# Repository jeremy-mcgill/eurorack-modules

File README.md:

# Eurorack Modules

## BufferedMult
A 1-in 4-out buffered multiple using a TL084 quad op-amp. 

## Clock
**Note: this is a work in progress, untested and unbuilt**

A master clock/divider module built around an Arduino Nano. 

## Mixer
**Note: this is a work in progress, untested and unbuilt**

A 4-input mixer based on a TL082 dual op-amp, with individual input gain controls and a master output control.

## PassiveMult
Dual passive 1-in 3-out multiples. Bottom section is normalled to top input, so the module can also be used as a single 1-in 6-out multiple. 

## Sequencer
**Note: this is a work in progress, untested and unbuilt**

An 8/16 step sequencer built around an Arduino Nano.

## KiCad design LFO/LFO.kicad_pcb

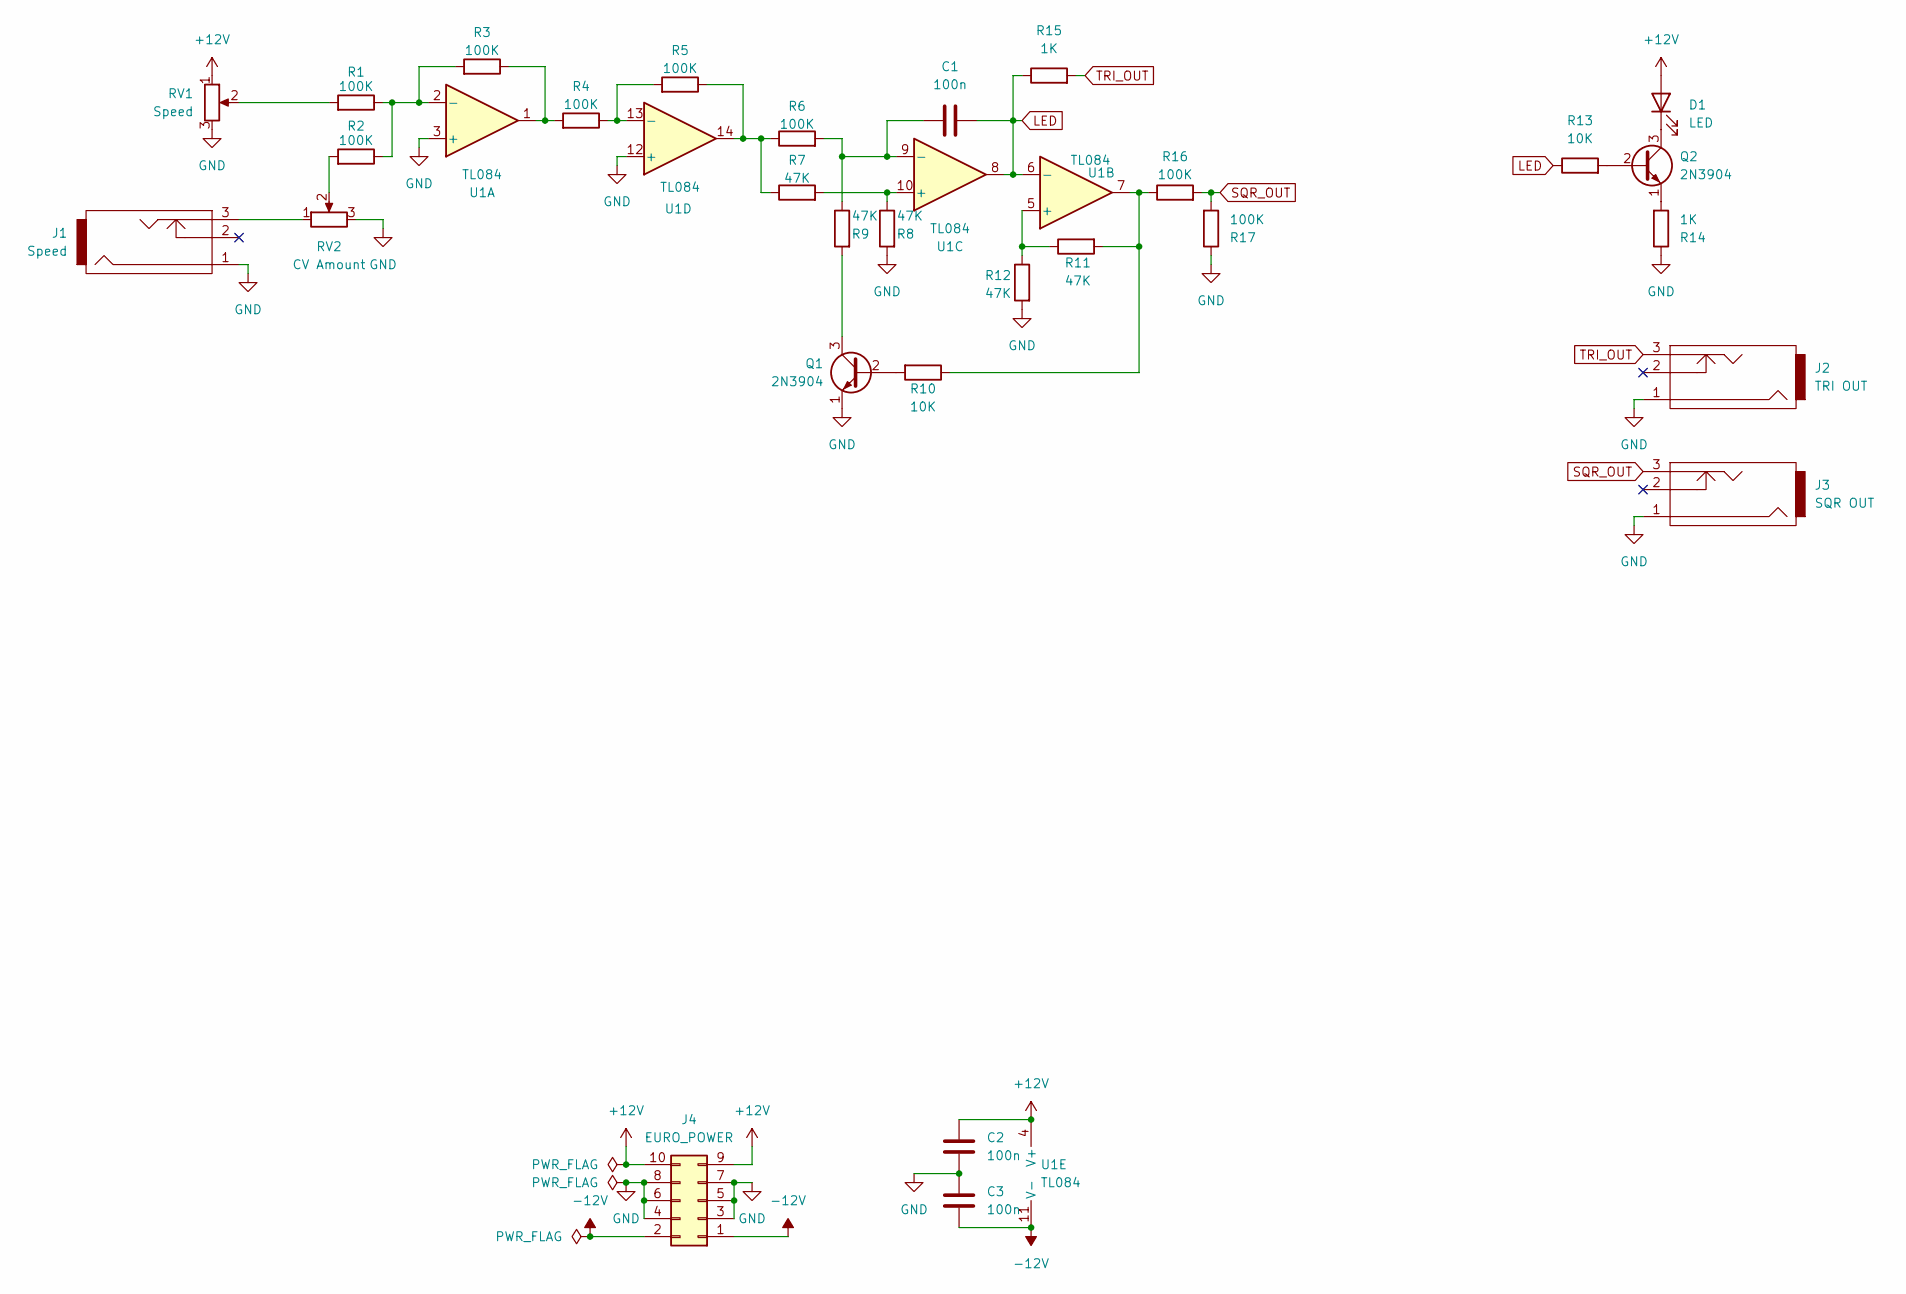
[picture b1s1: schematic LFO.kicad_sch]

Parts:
C1, C2, C3: 100n; C_Disc_D4.7mm_W2.5mm_P5.00mm
D1: LED; LED_D5.0mm
J1: Speed; PJ301M-12
J2: TRI OUT; PJ301M-12
J3: SQR OUT; PJ301M-12
J4: EURO_POWER; PinHeader_2x05_P2.54mm_Vertical
Q1, Q2: 2N3904; TO-92_Inline
R1, R2, R3, R4, R5, R6, R16, R17: 100K; R_Axial_DIN0207_L6.3mm_D2.5mm_P2.54mm_Vertical
R7, R8, R9, R11, R12: 47K; R_Axial_DIN0207_L6.3mm_D2.5mm_P2.54mm_Vertical
R10, R13: 10K; R_Axial_DIN0207_L6.3mm_D2.5mm_P2.54mm_Vertical
R14, R15: 1K; R_Axial_DIN0207_L6.3mm_D2.5mm_P2.54mm_Vertical
RV1: Speed; Potentiometer_Bourns_PTV09A-1_Single_Vertical
RV2: CV Amount; Potentiometer_Bourns_PTV09A-1_Single_Vertical
U1: TL084; DIP-14_W7.62mm_Socket

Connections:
+12V: C2.1, D1.2 (A), J4.9, J4.10, RV1.1, U1.4 (V+)
-12V: C3.2, J4.1, J4.2, U1.11 (V-)
GND: C2.2, C3.1, J1.1, J2.1, J3.1, J4.3, J4.4, J4.5, J4.6, J4.7, J4.8, Q1.1 (E), R8.2, R12.2, R14.1, R17.1, RV1.3, RV2.3, U1.3 (+), U1.12 (+)
LED: C1.2, R13.1, R15.1, U1.6 (-), U1.8
unnamed: D1.1 (K), Q2.3 (C)
unnamed: J1.3, RV2.1
unnamed: Q1.2 (B), R10.2
unnamed: Q1.3 (C), R9.2
unnamed: Q2.2 (B), R13.2
unnamed: Q2.1 (E), R14.2
unnamed: R1.2, RV1.2
unnamed: R2.2, RV2.2
unnamed: R3.1, R4.2, U1.1
unnamed: R5.1, R6.1, R7.1, U1.14
unnamed: R10.1, R11.2, R16.1, U1.7
unnamed: R1.1, R2.1, R3.2, U1.2 (-)
unnamed: R11.1, R12.1, U1.5 (+)
unnamed: R7.2, R8.1, U1.10 (+)
unnamed: C1.1, R6.2, R9.1, U1.9 (-)
unnamed: R4.1, R5.2, U1.13 (-)
SQR_OUT: J3.3, R16.2, R17.2
TRI_OUT: J2.3, R15.2

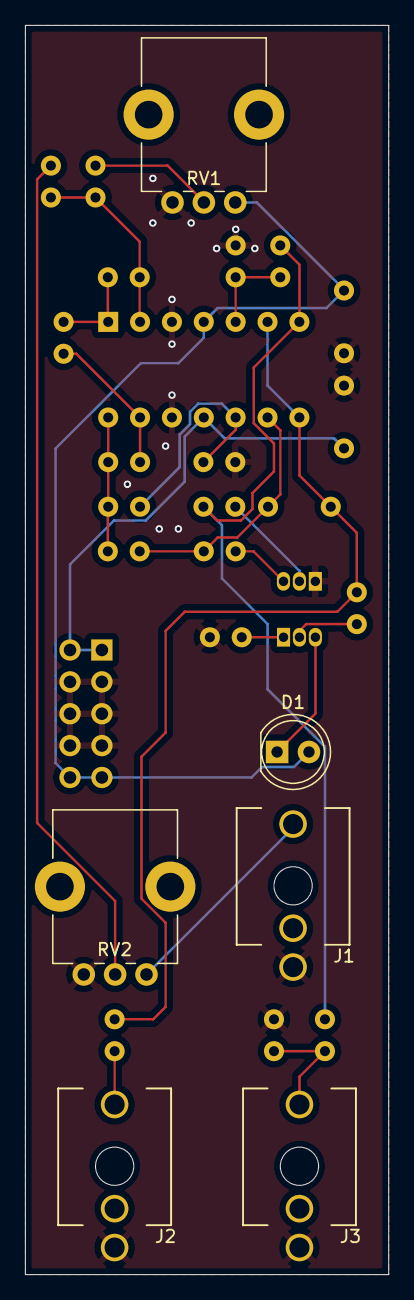
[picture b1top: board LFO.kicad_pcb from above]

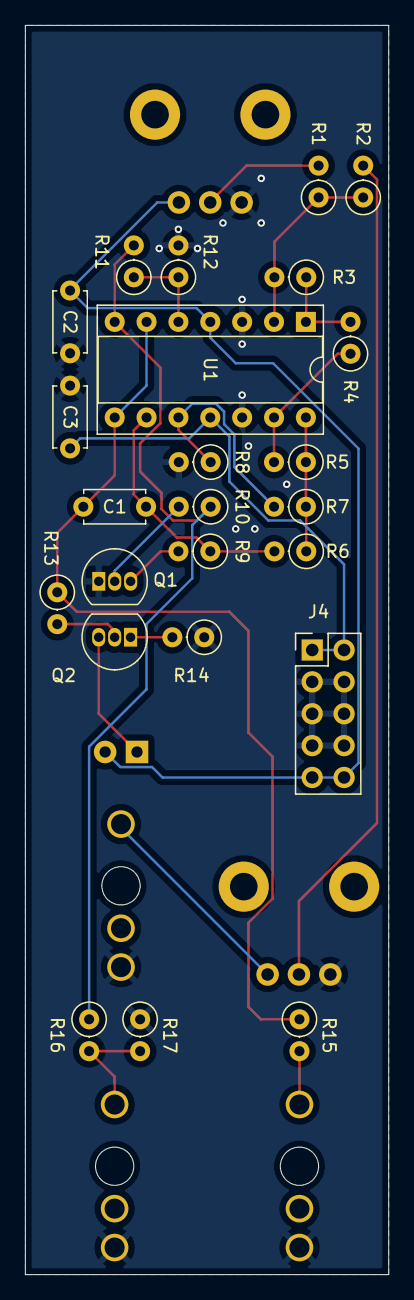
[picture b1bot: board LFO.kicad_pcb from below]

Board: 2 copper layers, 29.0 x 99.6 mm, 30 parts (24 on the bottom side), 22 nets.

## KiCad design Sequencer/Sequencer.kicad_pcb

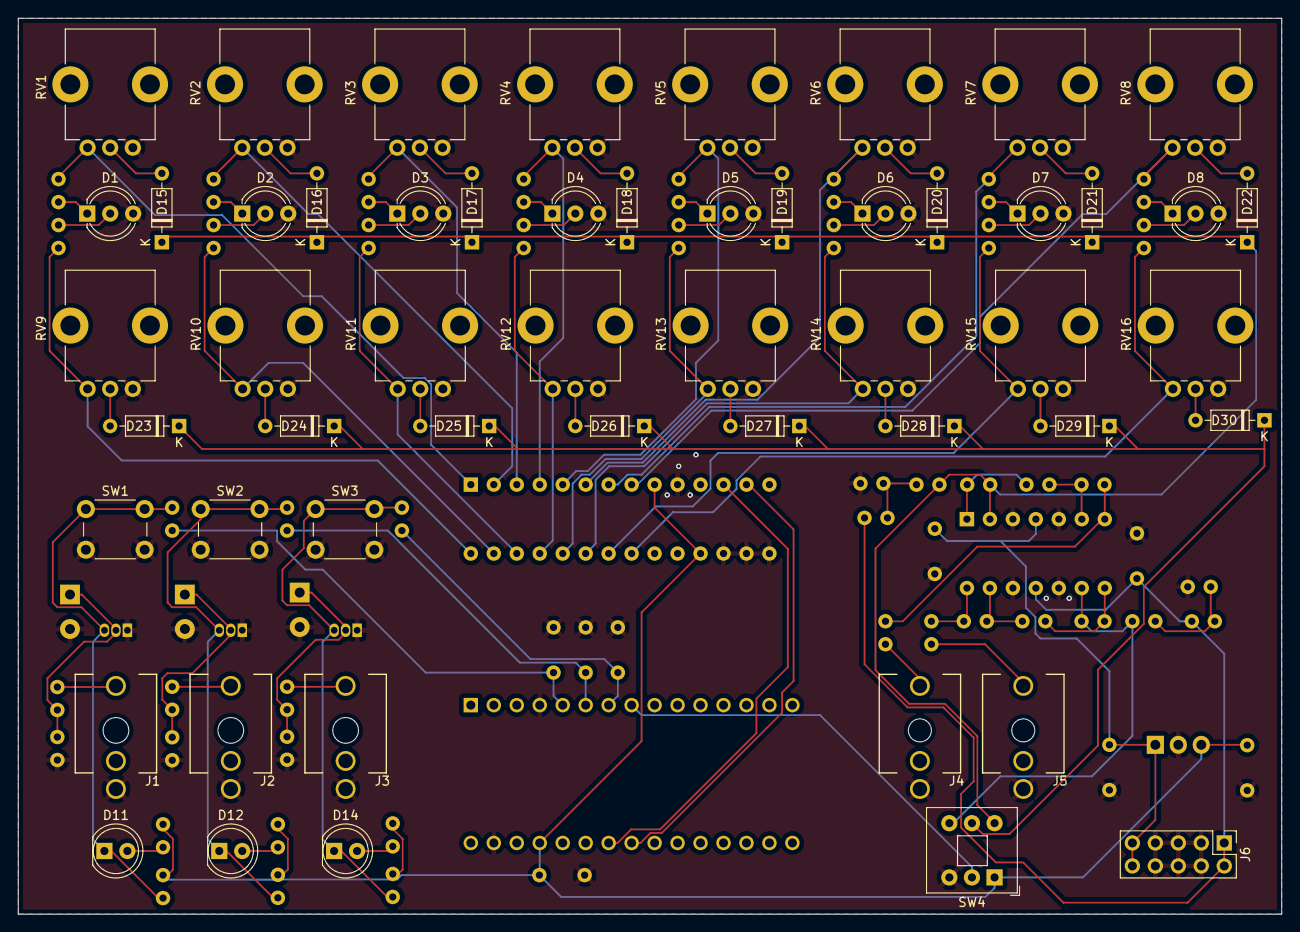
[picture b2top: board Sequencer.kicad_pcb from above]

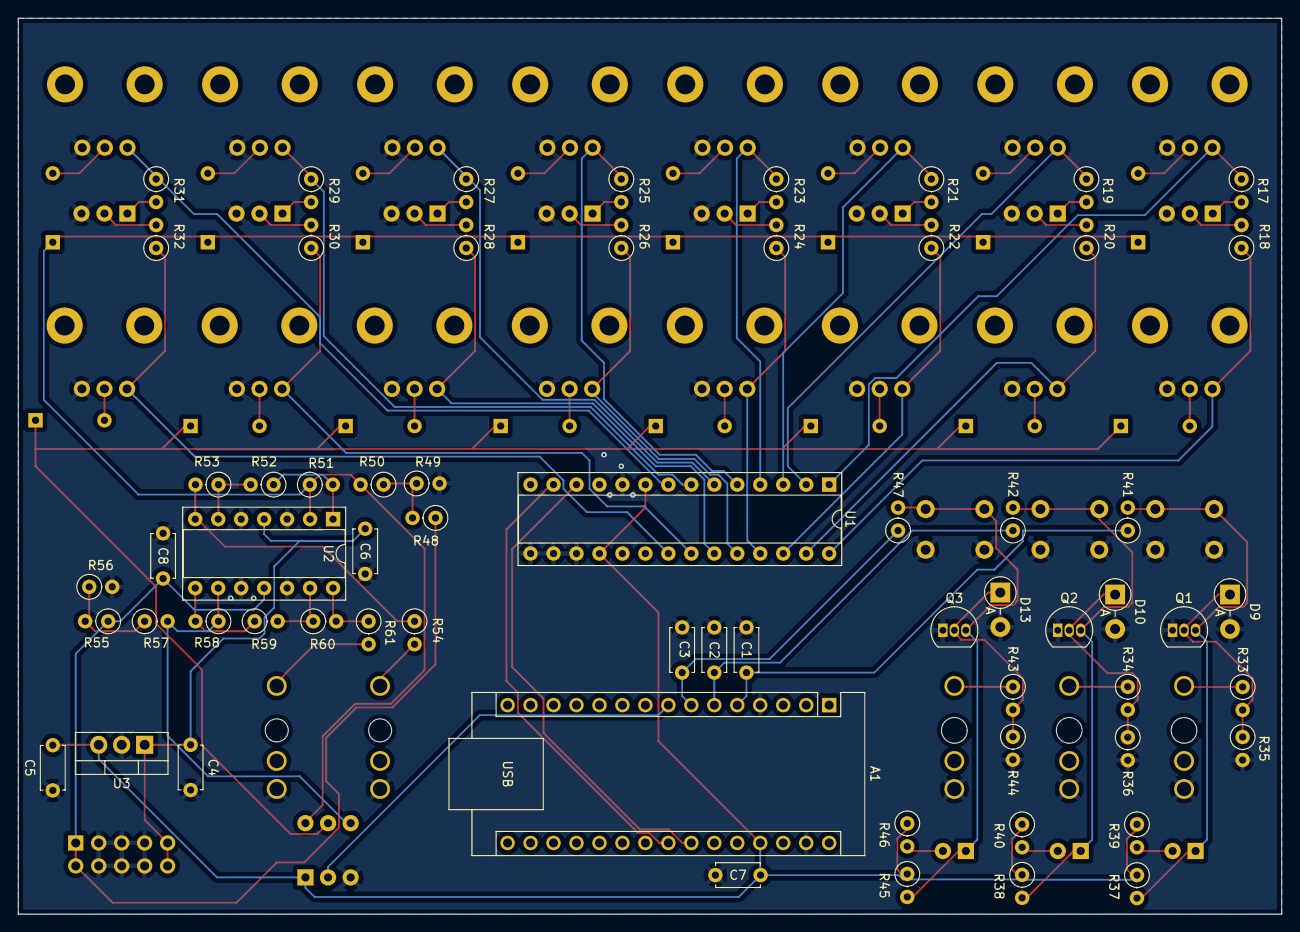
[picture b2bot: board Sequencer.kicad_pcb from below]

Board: 2 copper layers, 139.7 x 99.1 mm, 116 parts (63 on the bottom side), 83 nets.

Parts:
A1: Arduino_Nano_v3.x; Arduino_Nano
C1, C2, C3: 220nF; C_Disc_D4.7mm_W2.5mm_P5.00mm
C4: .33uF; C_Disc_D4.7mm_W2.5mm_P5.00mm
C5: .1uF; C_Disc_D4.7mm_W2.5mm_P5.00mm
C6, C7, C8: 100n; C_Disc_D4.7mm_W2.5mm_P5.00mm
D1, D2, D3, D4, D5, D6, D7, D8: LED_Dual_AAK; LED_D5.0mm-3
D9, D10, D13: 1N5817; D_DO-41_SOD81_P3.81mm_Vertical_AnodeUp
D11: LED_STEP; LED_D5.0mm_Clear
D12: LED_RESET; LED_D5.0mm_Clear
D14: LED_FLIP; LED_D5.0mm_Clear
D15, D16, D17, D18, D19, D20, D21, D22, D23, D24, D25, D26, D27, D28, D29, D30: 1N4148; D_DO-35_SOD27_P7.62mm_Horizontal
J1: CLOCK_IN; PJ301M-12
J2: RESET_IN; PJ301M-12
J3: FLIP_IN; PJ301M-12
J4: CV1_OUT; PJ301M-12
J5: CV2_OUT; PJ301M-12
J6: Power; PinHeader_2x05_P2.54mm_Vertical
Q1, Q2, Q3: 2N3904; TO-92_Inline
R17, R18, R19, R20, R21, R22, R23, R24, R25, R26, R27, R28, R29, R30, R31, R32, R39, R40, R46: 560R; R_Axial_DIN0207_L6.3mm_D2.5mm_P2.54mm_Vertical
R33, R34, R43, R50, R57: 100K; R_Axial_DIN0207_L6.3mm_D2.5mm_P2.54mm_Vertical
R35, R36, R44: 1M; R_Axial_DIN0207_L6.3mm_D2.5mm_P2.54mm_Vertical
R37, R38, R45, R52, R53, R59, R60: 10K; R_Axial_DIN0207_L6.3mm_D2.5mm_P2.54mm_Vertical
R41, R42, R47, R54, R61: 1K; R_Axial_DIN0207_L6.3mm_D2.5mm_P2.54mm_Vertical
R48, R55: 68K; R_Axial_DIN0207_L6.3mm_D2.5mm_P2.54mm_Vertical
R49, R56: 18K; R_Axial_DIN0207_L6.3mm_D2.5mm_P2.54mm_Vertical
R51, R58: 220K; R_Axial_DIN0207_L6.3mm_D2.5mm_P2.54mm_Vertical
RV1, RV2, RV3, RV4, RV5, RV6, RV7, RV8, RV9, RV10, RV11, RV12, RV13, RV14, RV15, RV16: A10K; Potentiometer_Bourns_PTV09A-1_Single_Vertical
SW1: SW_STEP; SW_PUSH_6mm
SW2: SW_RESET; SW_PUSH_6mm
SW3: SW_FLIP; SW_PUSH_6mm
SW4: SW_8/16; SW_Push_2P2T_Toggle_CK_PVA2xxH2xxxxxxV2
U1: MCP23017_SP; DIP-28_W7.62mm_Socket
U2: TL084; DIP-14_W7.62mm_Socket
U3: L7805; TO-220-3_Vertical

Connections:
+5V: A1.27 (+5V), C5.1, C7.1, R37.1, R38.1, R39.1, R40.1, R45.1, R46.1, SW4.1 (A), U1.9 (VDD), U1.18 (~RESET), U3.3 (OUT)
+12V: C4.1, C6.1, J6.9, J6.10, U2.4 (V+), U3.1 (IN)
-12V: C8.2, J6.1, J6.2, R48.1, R55.1, U2.11 (V-)
CLOCK_IN: A1.5 (D2), C1.1, R41.1
CV1_OUT: D15.1 (K), D16.1 (K), D17.1 (K), D18.1 (K), D19.1 (K), D20.1 (K), D21.1 (K), D22.1 (K), R50.2, R51.1, SW4.4 (A), U2.2 (-)
CV2_OUT: R57.2, R58.1, SW4.6 (C), U2.9 (-)
FLIP_IN: A1.7 (D4), C3.1, R47.1
GND: A1.4 (GND), A1.29 (GND), C1.2, C2.2, C3.2, C4.2, C5.2, C6.2, C7.2, C8.1, D1.3 (K), D2.3 (K), D3.3 (K), D4.3 (K), D5.3 (K), D6.3 (K), D7.3 (K), D8.3 (K), D9.2 (A), D10.2 (A), D13.2 (A), J1.1, J2.1, J3.1, J4.1, J5.1, J6.3, J6.4, J6.5, J6.6, J6.7, J6.8, Q1.1 (E), Q2.1 (E), Q3.1 (E), R35.2, R36.2, R44.2, R49.2, R56.2, RV1.1, RV2.1, RV3.1, RV4.1, RV5.1, RV6.1, RV7.1, RV8.1, RV9.1, RV10.1, RV11.1, RV12.1, RV13.1, RV14.1, RV15.1, RV16.1, SW1.2, SW2.2, SW3.2, SW4.3 (C), U1.10 (VSS), U1.15 (A0), U1.16 (A1), U1.17 (A2), U2.3 (+), U2.5 (+), U2.10 (+), U2.12 (+), U3.2 (GND)
unnamed: D1.1 (A1), R17.2
unnamed: D1.2 (A2), R18.2
unnamed: D2.1 (A1), R19.2
unnamed: D2.2 (A2), R20.2
unnamed: D3.1 (A1), R21.2
unnamed: D3.2 (A2), R22.2
unnamed: D4.1 (A1), R23.2
unnamed: D4.2 (A2), R24.2
unnamed: D5.1 (A1), R25.2
unnamed: D5.2 (A2), R26.2
unnamed: D6.1 (A1), R27.2
unnamed: D6.2 (A2), R28.2
unnamed: D7.1 (A1), R29.2
unnamed: D7.2 (A2), R30.2
unnamed: D8.1 (A1), R31.2
unnamed: D8.2 (A2), R32.2
unnamed: D9.1 (K), Q1.2 (B), R33.2, R35.1
unnamed: D10.1 (K), Q2.2 (B), R34.2, R36.1
unnamed: D11.2 (A), R39.2
unnamed: D11.1 (K), Q1.3 (C), R37.2, R41.2, SW1.1
unnamed: D12.2 (A), R40.2
unnamed: D12.1 (K), Q2.3 (C), R38.2, R42.2, SW2.1
unnamed: D13.1 (K), Q3.2 (B), R43.2, R44.1
unnamed: D14.2 (A), R46.2
unnamed: D14.1 (K), Q3.3 (C), R45.2, R47.2, SW3.1
unnamed: D15.2 (A), RV1.2
unnamed: D16.2 (A), RV2.2
unnamed: D17.2 (A), RV3.2
unnamed: D18.2 (A), RV4.2
unnamed: D19.2 (A), RV5.2
unnamed: D20.2 (A), RV6.2
unnamed: D21.2 (A), RV7.2
unnamed: D22.2 (A), RV8.2
unnamed: D23.2 (A), RV9.2
unnamed: D23.1 (K), D24.1 (K), D25.1 (K), D26.1 (K), D27.1 (K), D28.1 (K), D29.1 (K), D30.1 (K), SW4.5 (B)
unnamed: D24.2 (A), RV10.2
unnamed: D25.2 (A), RV11.2
unnamed: D26.2 (A), RV12.2
unnamed: D27.2 (A), RV13.2
unnamed: D28.2 (A), RV14.2
unnamed: D29.2 (A), RV15.2
unnamed: D30.2 (A), RV16.2
unnamed: J1.3, R33.1
unnamed: J2.3, R34.1
unnamed: J3.3, R43.1
unnamed: J4.3, R54.2
unnamed: J5.3, R61.2
unnamed: R48.2, R49.1, R50.1
unnamed: R51.2, R52.1, U2.1
unnamed: R53.2, R54.1, U2.7
unnamed: R55.2, R56.1, R57.1
unnamed: R58.2, R59.1, U2.8
unnamed: R60.2, R61.1, U2.14
unnamed: R52.2, R53.1, U2.6 (-)
unnamed: R59.2, R60.1, U2.13 (-)
RESET_IN: A1.6 (D3), C2.1, R42.1
SCK: A1.24 (A5), U1.12 (SCK)
SDA: A1.23 (A4), U1.13 (SDA)
STEP1: R17.1, RV1.3, U1.1 (GPB0)
STEP2: R19.1, RV2.3, U1.2 (GPB1)
STEP3: R21.1, RV3.3, U1.3 (GPB2)
STEP4: R23.1, RV4.3, U1.4 (GPB3)
STEP5: R25.1, RV5.3, U1.5 (GPB4)
STEP6: R27.1, RV6.3, U1.6 (GPB5)
STEP7: R29.1, RV7.3, U1.7 (GPB6)
STEP8: R31.1, RV8.3, U1.8 (GPB7)
STEP9: R18.1, RV9.3, U1.28 (GPA7)
STEP10: R20.1, RV10.3, U1.27 (GPA6)
STEP11: R22.1, RV11.3, U1.26 (GPA5)
STEP12: R24.1, RV12.3, U1.25 (GPA4)
STEP13: R26.1, RV13.3, U1.24 (GPA3)
STEP14: R28.1, RV14.3, U1.23 (GPA2)
STEP15: R30.1, RV15.3, U1.22 (GPA1)
STEP16: R32.1, RV16.3, U1.21 (GPA0)
STEP_MODE: A1.8 (D5), SW4.2 (B)

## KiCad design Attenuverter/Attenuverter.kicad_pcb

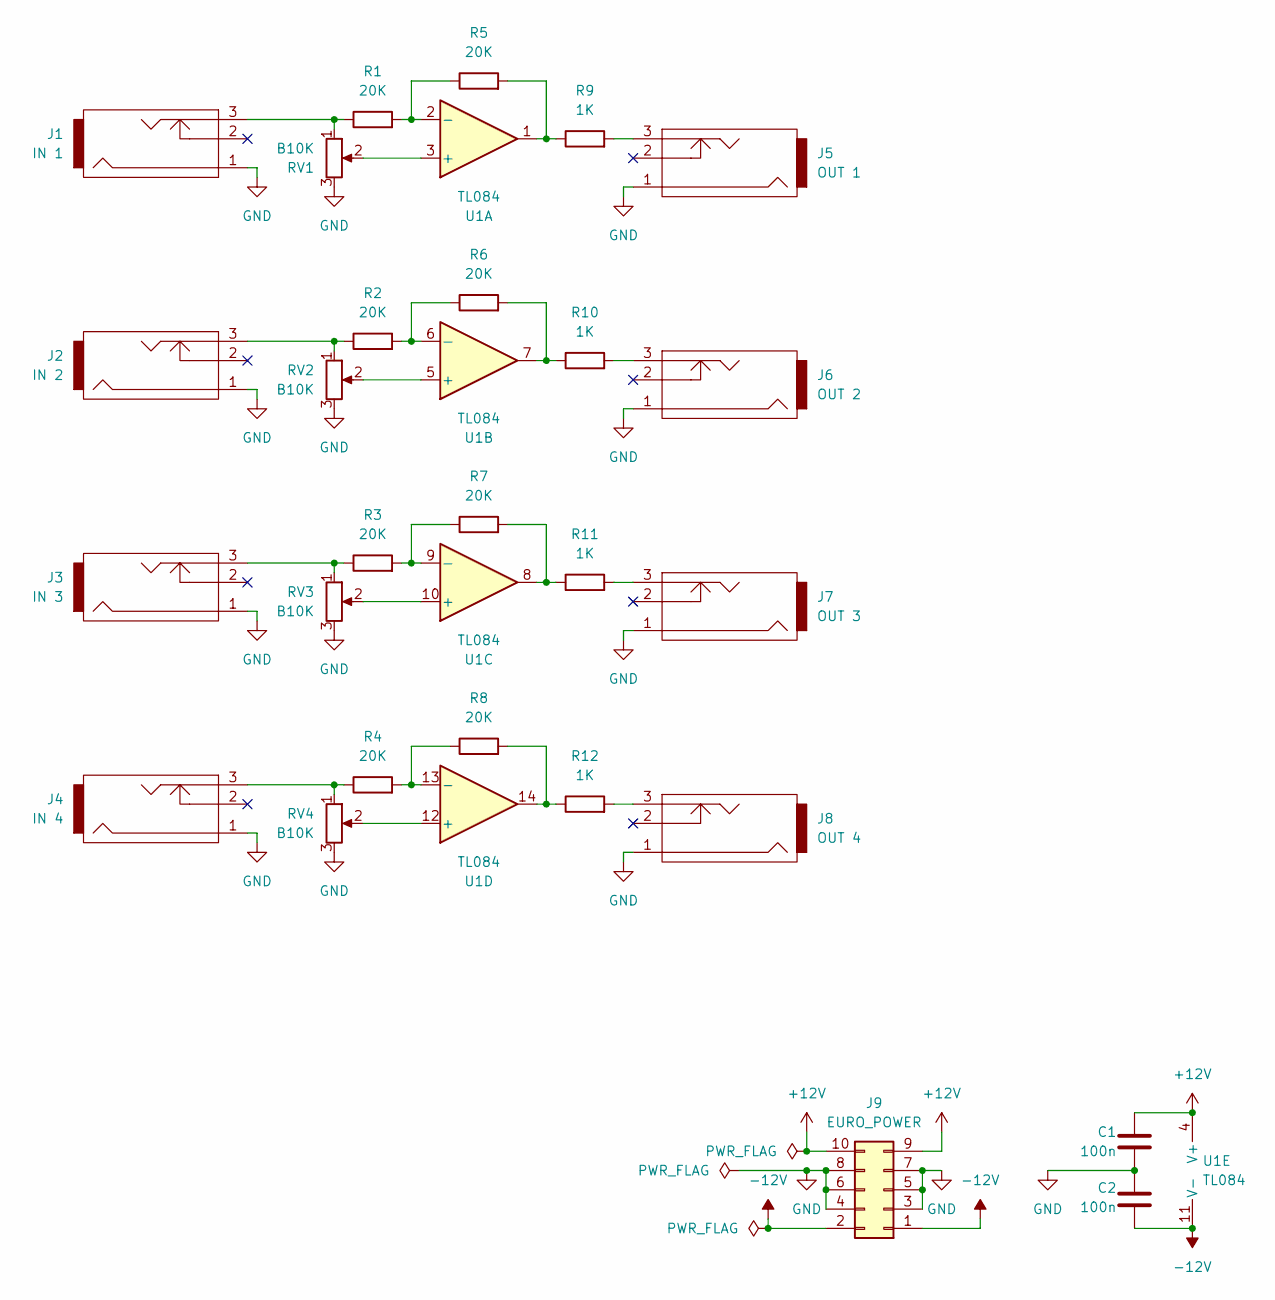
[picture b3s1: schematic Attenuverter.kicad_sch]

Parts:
C1, C2: 100n; C_Disc_D3.0mm_W1.6mm_P2.50mm
J1: IN 1; PJ301M-12
J2: IN 2; PJ301M-12
J3: IN 3; PJ301M-12
J4: IN 4; PJ301M-12
J5: OUT 1; PJ301M-12
J6: OUT 2; PJ301M-12
J7: OUT 3; PJ301M-12
J8: OUT 4; PJ301M-12
J9: EURO_POWER; PinHeader_2x05_P2.54mm_Vertical
R1, R2, R3, R4, R5, R6, R7, R8: 20K; R_Axial_DIN0204_L3.6mm_D1.6mm_P2.54mm_Vertical
R9, R10, R11, R12: 1K; R_Axial_DIN0204_L3.6mm_D1.6mm_P2.54mm_Vertical
RV1, RV2, RV3, RV4: B10K; Potentiometer_Bourns_PTV09A-1_Single_Vertical
U1: TL084; DIP-14_W7.62mm_Socket

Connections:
+12V: C1.1, J9.9, J9.10, U1.4 (V+)
-12V: C2.2, J9.1, J9.2, U1.11 (V-)
GND: C1.2, C2.1, J1.1, J2.1, J3.1, J4.1, J5.1, J6.1, J7.1, J8.1, J9.3, J9.4, J9.5, J9.6, J9.7, J9.8, RV1.3, RV2.3, RV3.3, RV4.3
unnamed: J1.3, R1.1, RV1.1
unnamed: J2.3, R2.1, RV2.1
unnamed: J3.3, R3.1, RV3.1
unnamed: J4.3, R4.1, RV4.1
unnamed: J5.3, R9.2
unnamed: J6.3, R10.2
unnamed: J7.3, R11.2
unnamed: J8.3, R12.2
unnamed: R5.2, R9.1, U1.1
unnamed: R6.2, R10.1, U1.7
unnamed: R7.2, R11.1, U1.8
unnamed: R8.2, R12.1, U1.14
unnamed: RV1.2, U1.3 (+)
unnamed: R1.2, R5.1, U1.2 (-)
unnamed: RV2.2, U1.5 (+)
unnamed: R2.2, R6.1, U1.6 (-)
unnamed: RV3.2, U1.10 (+)
unnamed: R3.2, R7.1, U1.9 (-)
unnamed: RV4.2, U1.12 (+)
unnamed: R4.2, R8.1, U1.13 (-)

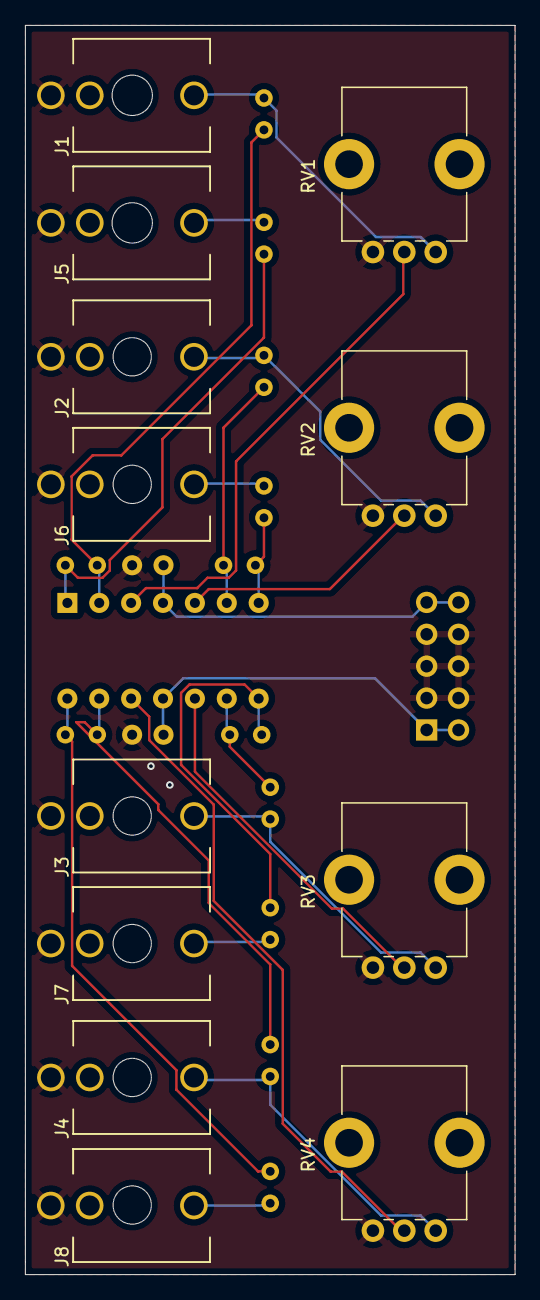
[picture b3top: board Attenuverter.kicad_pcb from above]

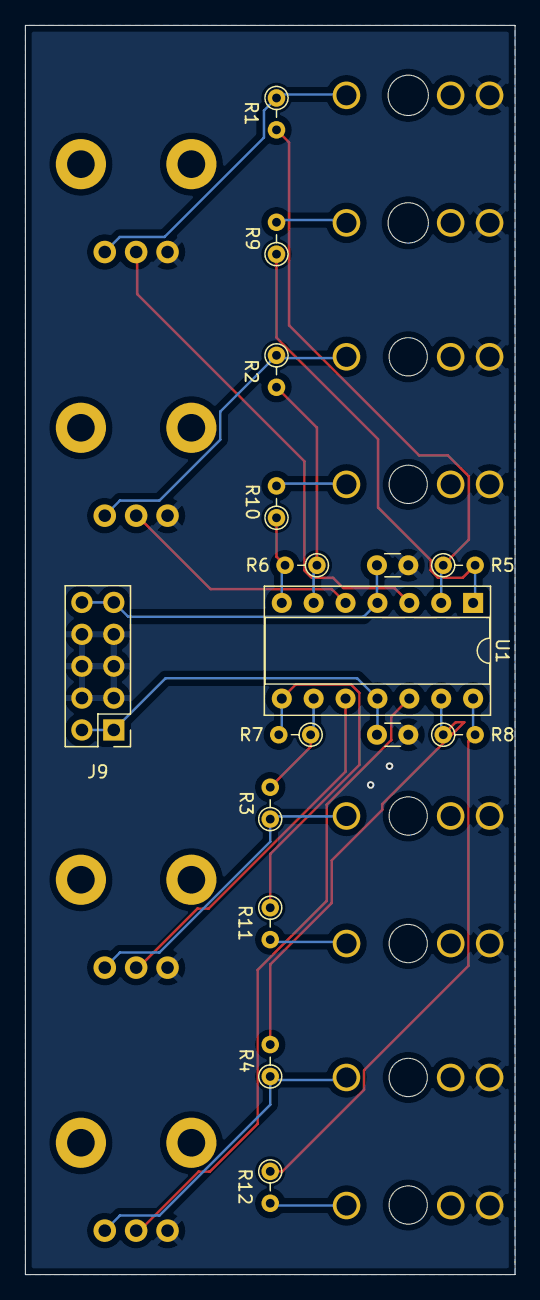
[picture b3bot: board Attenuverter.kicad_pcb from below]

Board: 2 copper layers, 39.0 x 99.5 mm, 28 parts (16 on the bottom side), 23 nets.

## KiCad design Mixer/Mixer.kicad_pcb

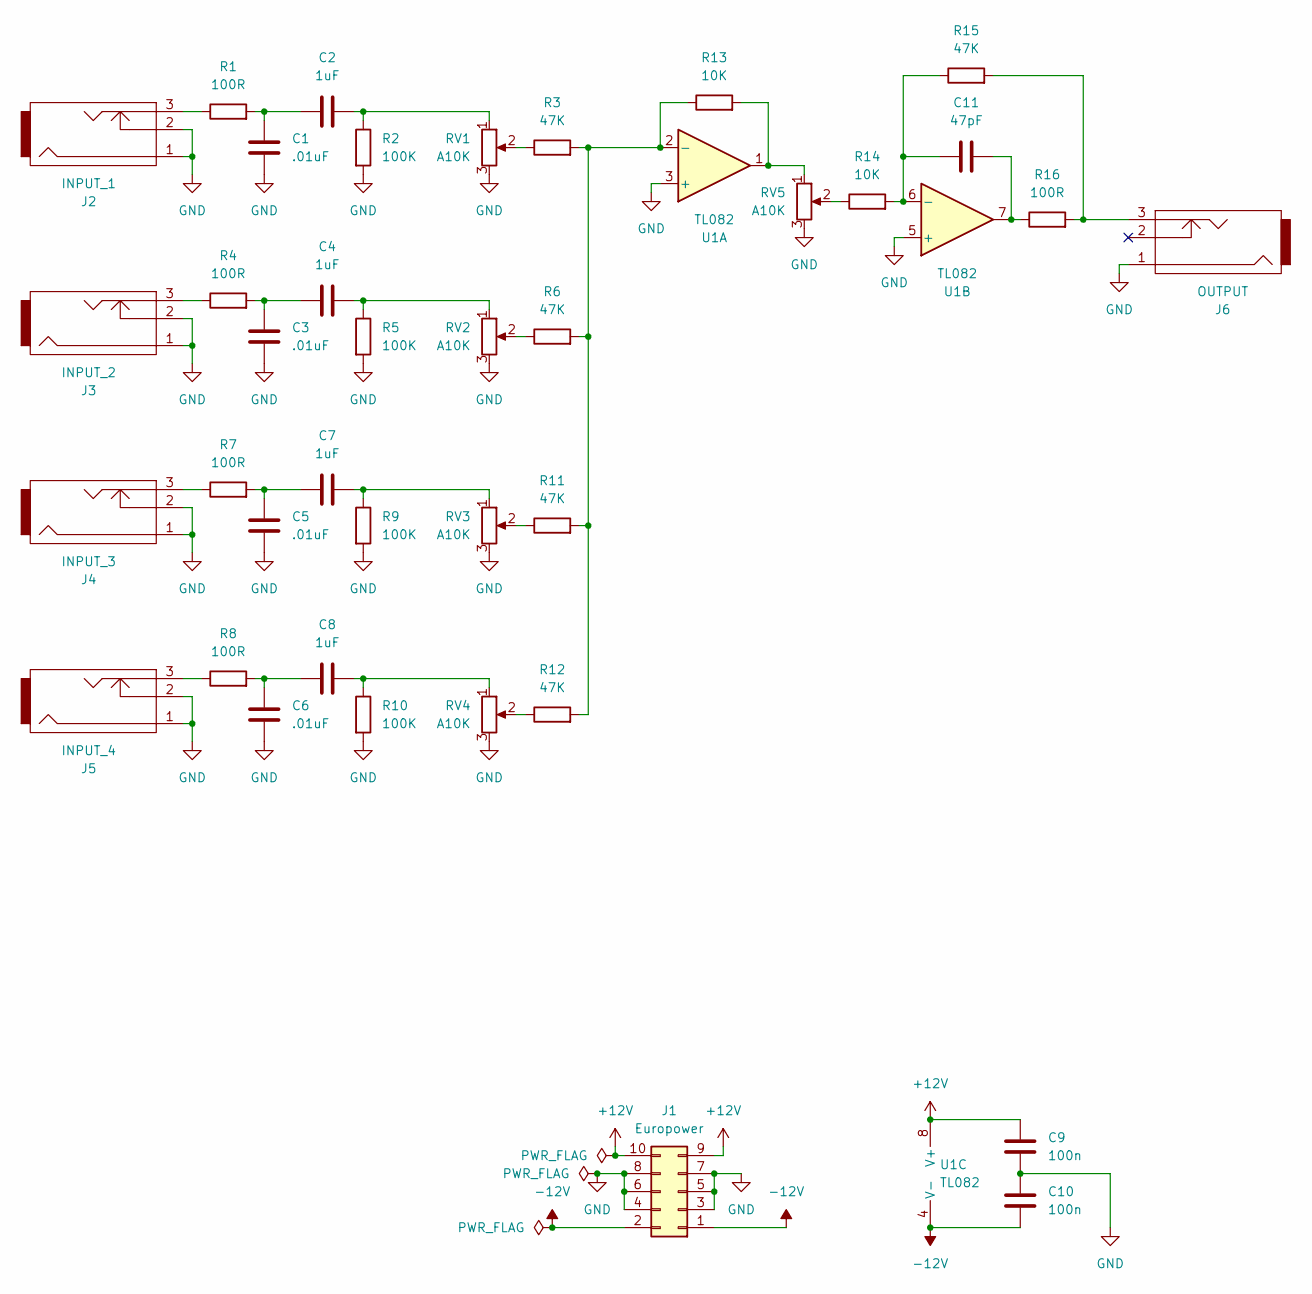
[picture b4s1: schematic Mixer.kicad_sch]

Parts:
C1, C3, C5, C6: .01uF; C_Disc_D4.7mm_W2.5mm_P5.00mm
C2, C4, C7, C8: 1uF; C_Disc_D4.7mm_W2.5mm_P5.00mm
C9, C10: 100n; C_Disc_D4.7mm_W2.5mm_P5.00mm
C11: 47pF; C_Disc_D4.7mm_W2.5mm_P5.00mm
J1: Europower; PinHeader_2x05_P2.54mm_Vertical
J2: INPUT_1; PJ301M-12
J3: INPUT_2; PJ301M-12
J4: INPUT_3; PJ301M-12
J5: INPUT_4; PJ301M-12
J6: OUTPUT; PJ301M-12
R1, R4, R7, R8, R16: 100R; R_Axial_DIN0207_L6.3mm_D2.5mm_P2.54mm_Vertical
R2, R5, R9, R10: 100K; R_Axial_DIN0207_L6.3mm_D2.5mm_P2.54mm_Vertical
R3, R6, R11, R12, R15: 47K; R_Axial_DIN0207_L6.3mm_D2.5mm_P2.54mm_Vertical
R13, R14: 10K; R_Axial_DIN0207_L6.3mm_D2.5mm_P2.54mm_Vertical
RV1, RV2, RV3, RV4, RV5: A10K; Potentiometer_Bourns_PTV09A-1_Single_Vertical
U1: TL082; DIP-8_W7.62mm_Socket

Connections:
+12V: C9.1, J1.9, J1.10, U1.8 (V+)
-12V: C10.2, J1.1, J1.2, U1.4 (V-)
GND: C1.2, C3.2, C5.2, C6.2, C9.2, C10.1, J1.3, J1.4, J1.5, J1.6, J1.7, J1.8, J2.1, J2.2, J3.1, J3.2, J4.1, J4.2, J5.1, J5.2, J6.1, R2.2, R5.2, R9.2, R10.2, RV1.3, RV2.3, RV3.3, RV4.3, RV5.3, U1.3 (+), U1.5 (+)
unnamed: C1.1, C2.1, R1.2
unnamed: C2.2, R2.1, RV1.1
unnamed: C3.1, C4.1, R4.2
unnamed: C4.2, R5.1, RV2.1
unnamed: C5.1, C7.1, R7.2
unnamed: C6.1, C8.1, R8.2
unnamed: C7.2, R9.1, RV3.1
unnamed: C8.2, R10.1, RV4.1
unnamed: C11.2, R16.1, U1.7
unnamed: J2.3, R1.1
unnamed: J3.3, R4.1
unnamed: J4.3, R7.1
unnamed: J5.3, R8.1
unnamed: J6.3, R15.2, R16.2
unnamed: R3.1, RV1.2
unnamed: R6.1, RV2.2
unnamed: R11.1, RV3.2
unnamed: R12.1, RV4.2
unnamed: R13.2, RV5.1, U1.1
unnamed: R14.1, RV5.2
unnamed: R3.2, R6.2, R11.2, R12.2, R13.1, U1.2 (-)
unnamed: C11.1, R14.2, R15.1, U1.6 (-)

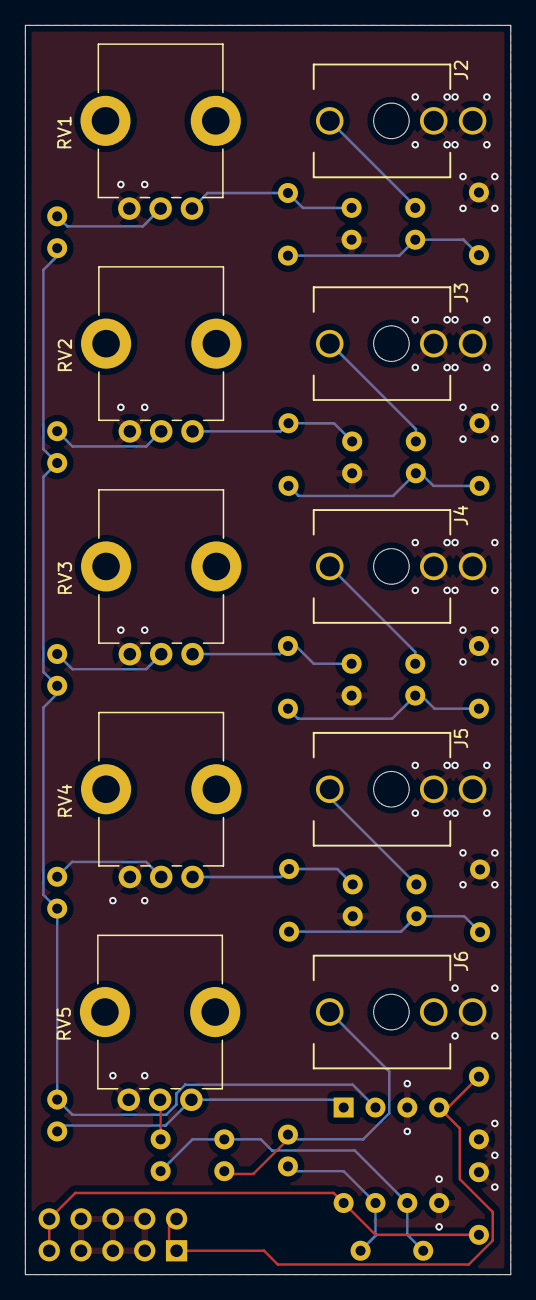
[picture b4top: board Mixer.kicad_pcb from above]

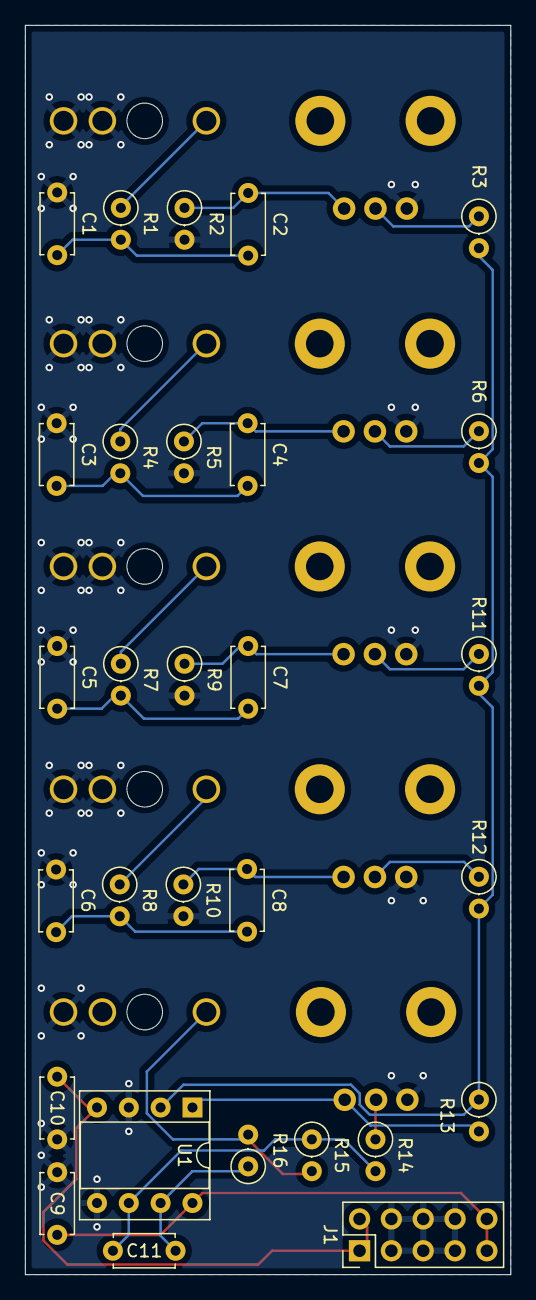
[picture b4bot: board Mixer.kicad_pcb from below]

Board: 2 copper layers, 38.7 x 99.7 mm, 39 parts (29 on the bottom side), 25 nets.

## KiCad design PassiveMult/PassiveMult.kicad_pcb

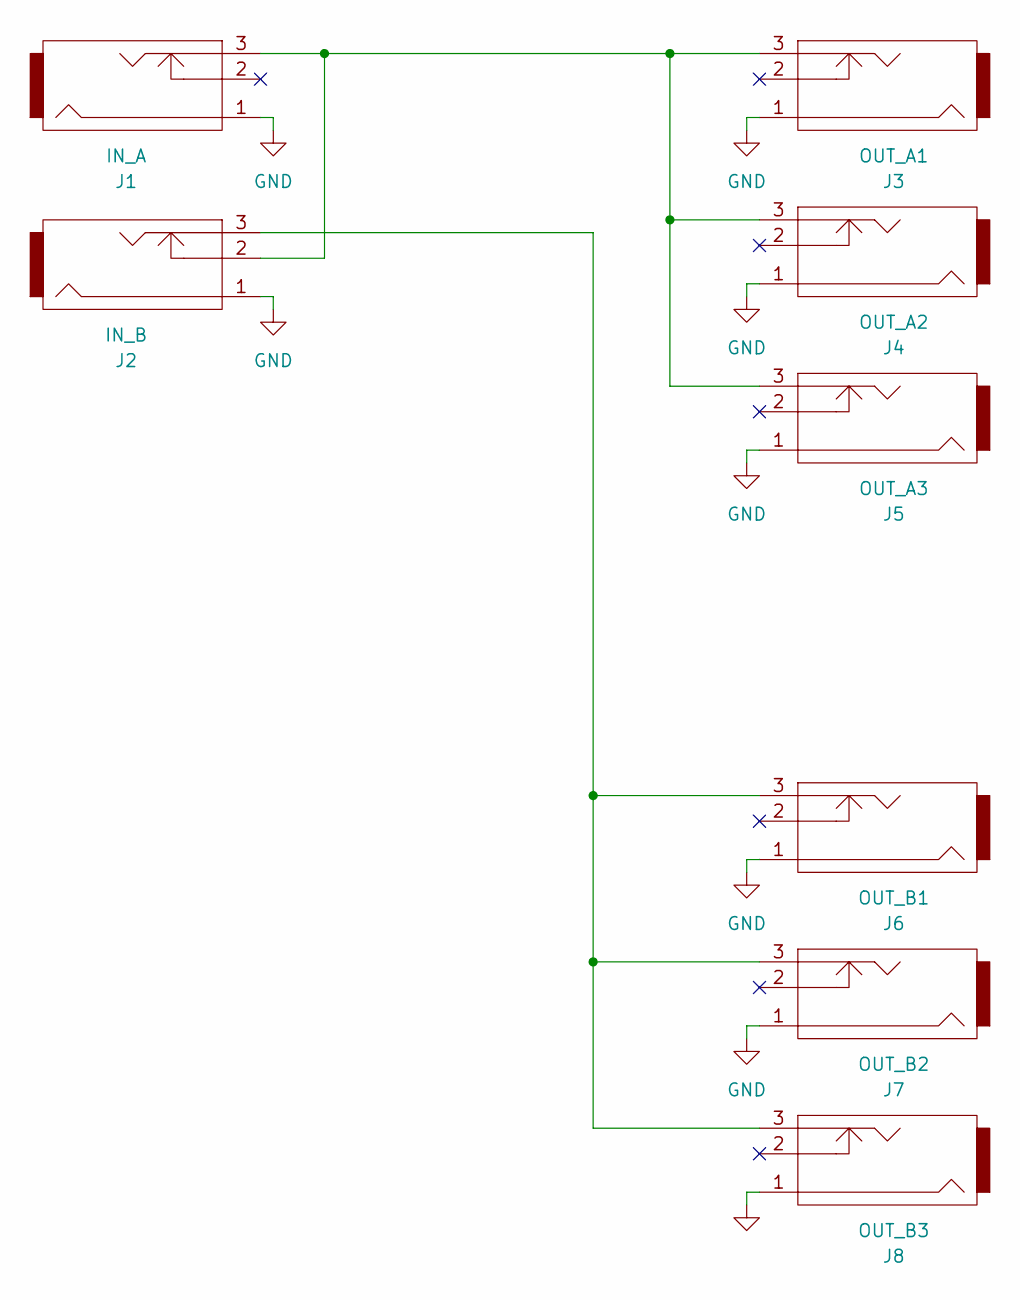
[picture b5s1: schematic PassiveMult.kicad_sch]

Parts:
J1: IN_A; PJ301M-12
J2: IN_B; PJ301M-12
J3: OUT_A1; PJ301M-12
J4: OUT_A2; PJ301M-12
J5: OUT_A3; PJ301M-12
J6: OUT_B1; PJ301M-12
J7: OUT_B2; PJ301M-12
J8: OUT_B3; PJ301M-12

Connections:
GND: J1.1, J2.1, J3.1, J4.1, J5.1, J6.1, J7.1, J8.1
unnamed: J1.3, J2.2, J3.3, J4.3, J5.3
unnamed: J2.3, J6.3, J7.3, J8.3

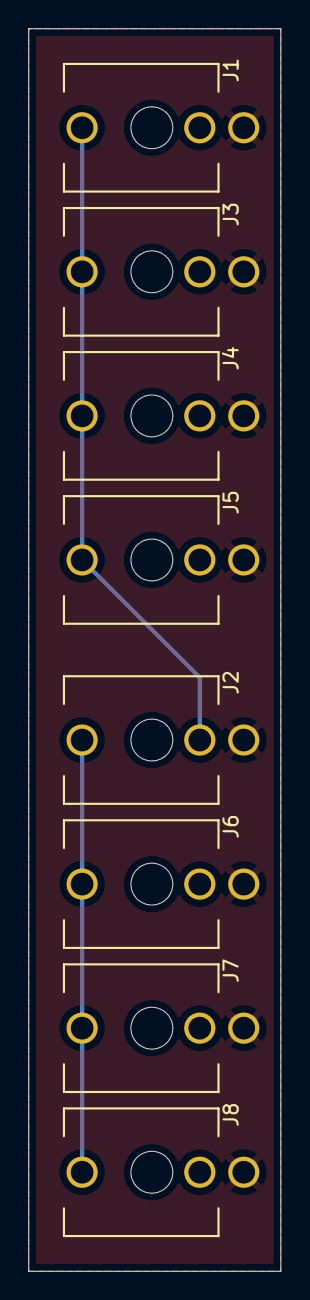
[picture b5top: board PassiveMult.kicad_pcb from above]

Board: 2 copper layers, 17.8 x 87.6 mm, 8 parts (0 on the bottom side), 3 nets.

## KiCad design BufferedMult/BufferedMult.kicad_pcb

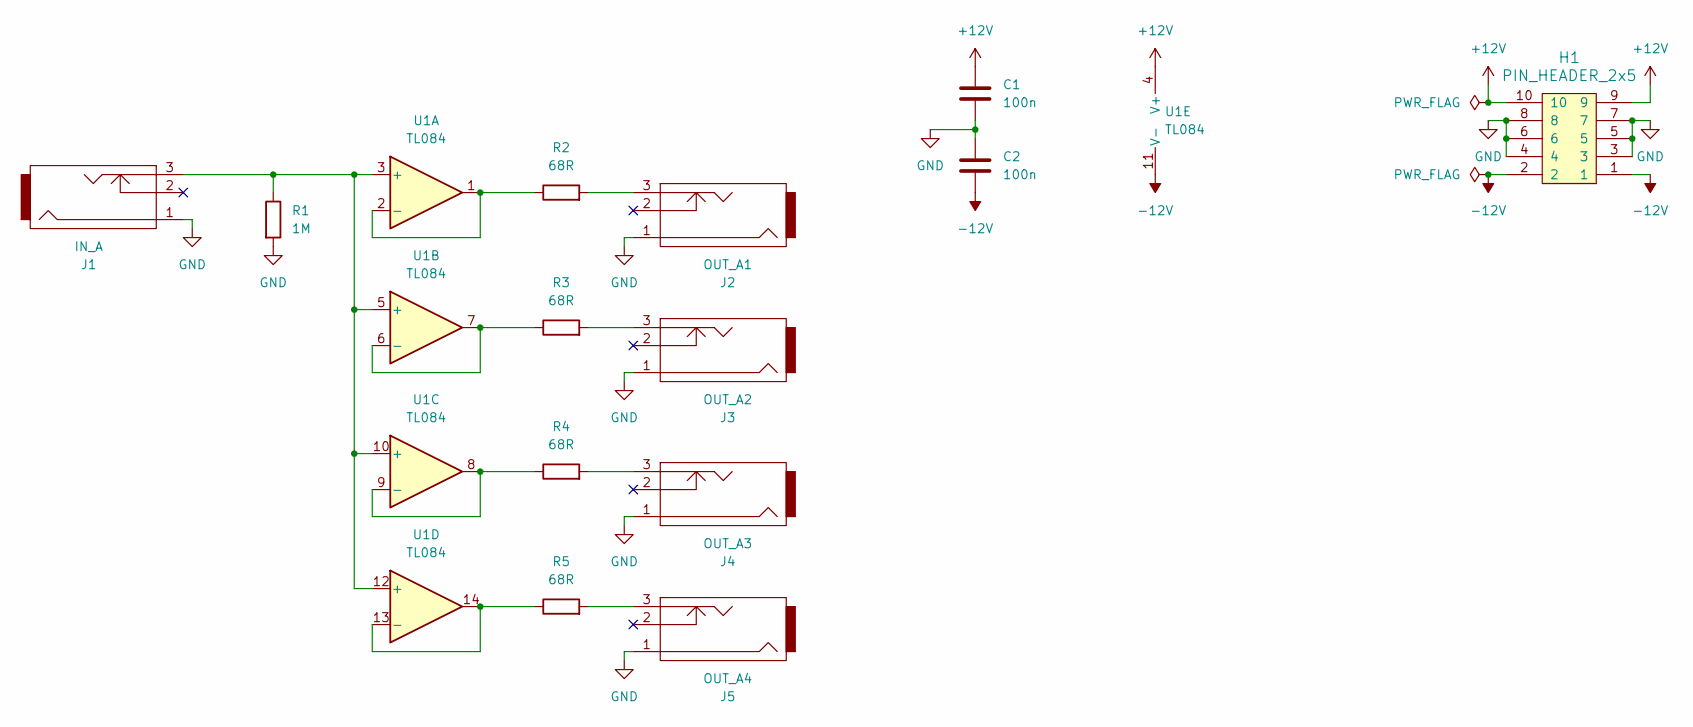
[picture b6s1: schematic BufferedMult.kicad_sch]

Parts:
C1, C2: 100n; C_Disc_D4.7mm_W2.5mm_P5.00mm
H1: PIN_HEADER_2x5; PinHeader_2x05_P2.54mm_Vertical
J1: IN_A; PJ301M-12
J2: OUT_A1; PJ301M-12
J3: OUT_A2; PJ301M-12
J4: OUT_A3; PJ301M-12
J5: OUT_A4; PJ301M-12
R1: 1M; R_Axial_DIN0207_L6.3mm_D2.5mm_P2.54mm_Vertical
R2, R3, R4, R5: 68R; R_Axial_DIN0207_L6.3mm_D2.5mm_P2.54mm_Vertical
U1: TL084; DIP-14_W7.62mm_Socket

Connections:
+12V: C1.1, H1.9, H1.10, U1.4 (V+)
-12V: C2.2, H1.1, H1.2, U1.11 (V-)
GND: C1.2, C2.1, H1.3, H1.4, H1.5, H1.6, H1.7, H1.8, J1.1, J2.1, J3.1, J4.1, J5.1, R1.2
unnamed: J2.3, R2.2
unnamed: J3.3, R3.2
unnamed: J4.3, R4.2
unnamed: J5.3, R5.2
unnamed: J1.3, R1.1, U1.3 (+), U1.5 (+), U1.10 (+), U1.12 (+)
unnamed: R2.1, U1.1, U1.2 (-)
unnamed: R3.1, U1.6 (-), U1.7
unnamed: R4.1, U1.8, U1.9 (-)
unnamed: R5.1, U1.13 (-), U1.14
